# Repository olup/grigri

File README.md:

# grigri
Grigri - the open storyteller

<p xmlns:cc="http://creativecommons.org/ns#" xmlns:dct="http://purl.org/dc/terms/"><a property="dct:title" rel="cc:attributionURL" href="https://github.com/olup/grigri">Grigri</a> by <a rel="cc:attributionURL dct:creator" property="cc:attributionName" href="https://github.com/olup">the grigri team</a> is licensed under <a href="http://creativecommons.org/licenses/by-nc/4.0/?ref=chooser-v1" target="_blank" rel="license noopener noreferrer" style="display:inline-block;">CC BY-NC 4.0</a></p>

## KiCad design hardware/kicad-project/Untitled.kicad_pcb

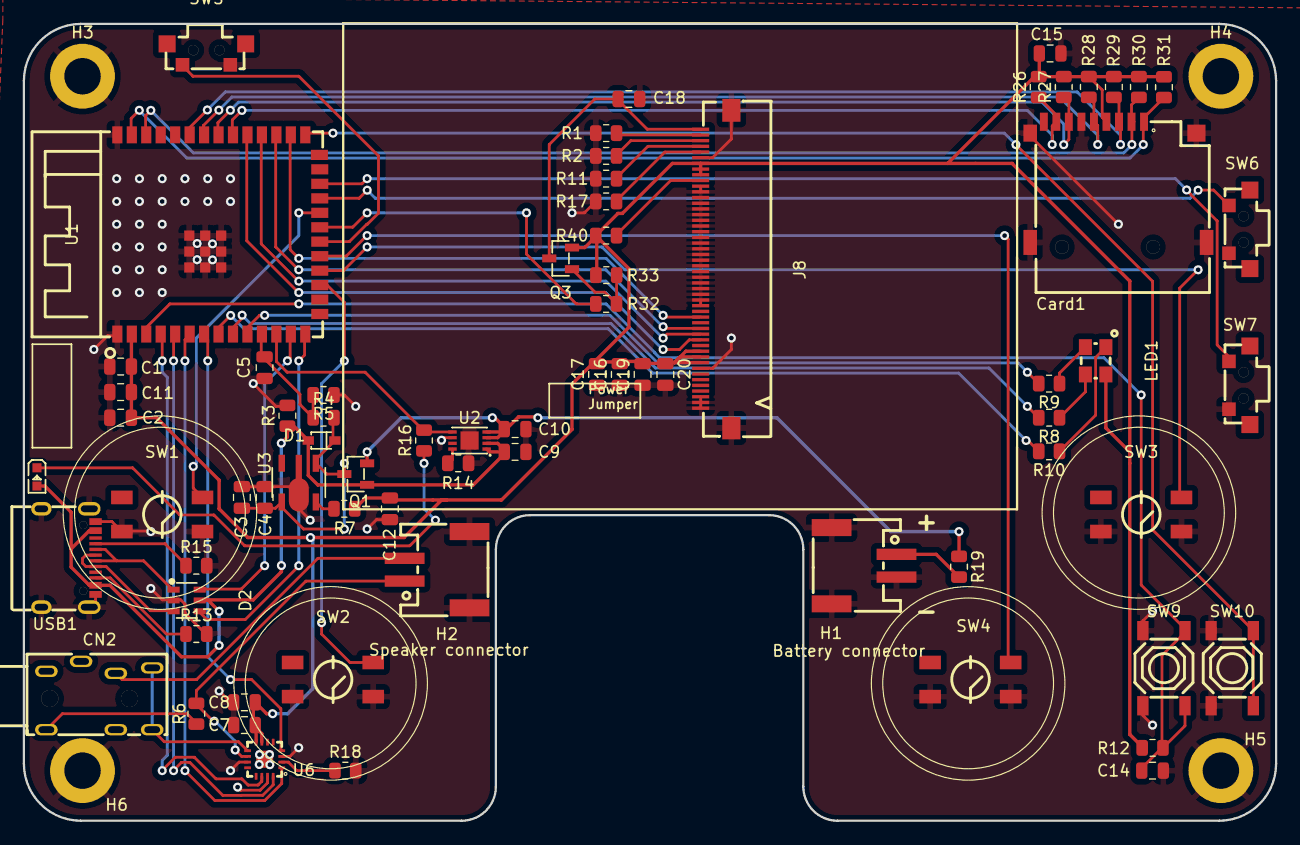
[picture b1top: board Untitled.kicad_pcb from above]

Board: 2 copper layers, 110.0 x 70.0 mm, 75 parts (0 on the bottom side), 59 nets.

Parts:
C1, C2, C3, C7, C15, C16, C17, C18, C19: 10uF; C_0805_2012Metric
C4, C12: 10uf; C_0805_2012Metric
C5, C20: 100nF; C_0805_2012Metric
C8: 0.1uF; C_0805_2012Metric
C9, C10: 4.7uF; C_0805_2012Metric
C11: 1uF; C_0805_2012Metric
C14: 1uf; C_0805_2012Metric
CHARGE_LED1: KT-0603R; LED0603-RD
CN2: ST-0322D00-071-1A2H; AUDIO-TH_ST-0322D00-071-1A2H
Card1: TF PUSH; TF-SMD_TF-PUSH
D1: 1N5819WS; SOD-323_L1.8-W1.3-LS2.5-RD
D2: USBLC6-2SC6_C2687116; SOT-23-6_L2.9-W1.6-P0.95-LS2.8-BL
H1: Battery connector; CONN-SMD_2P-P2.00_XUNPU_WAFER-PH2.0-2PWB
H2: Speaker connector; CONN-SMD_2P-P2.00_XUNPU_WAFER-PH2.0-2PWB
H3, H4, H5, H6: mhole; MountingHole_3.2mm_M3_ISO7380_Pad
J8: Conn_01x50; FPC-SMD_AFC01-S50FCC-00
LED1: E6C1209RGBC3UDA; LED-ARRAY-SMD_4P-L3.2-W2.7-TL-1
Q1, Q3: DMG2301L-7; SOT-23-3_L2.9-W1.3-P1.90-LS2.4-BR
R1, R2, R11, R17: 10; R_0805_2012Metric
R3, R12, R26, R27, R28, R29, R30, R31, R40: 10k; R_0805_2012Metric
R4, R5: 1M; R_0805_2012Metric
R6, R32: 330; R_0805_2012Metric
R7, R18, R19: 0; R_0805_2012Metric
R8, R9: 30; R_0805_2012Metric
R10: 120; R_0805_2012Metric
R13, R15: 5.1k; R_0805_2012Metric
R14: 3k; R_0805_2012Metric
R16: 2K2; R_0805_2012Metric
R33: 100k; R_0805_2012Metric
SW1, SW2, SW3, SW4: K2-1109SP-C4SA; KEY-SMD_4P-L4.5-W4.5-P3.00-LS7.0
SW5, SW6, SW7: GT-TC054C-H035-L1W; KEY-SMD_4P-L7.8-W2.8-P4.20-EH
SW9, SW10: TS-1187A-B-A-B; SW-SMD_4P-L5.1-W5.1-P3.70-LS6.5-TL-2
U1: ESP32-S3-WROOM-1(N8R2); WIRELM-SMD_ESP32-S3-WROOM-1
U2: MCP73831-2ACI/MC; TDFN-8_L3.0-W2.0-P0.50-BL-EP1.6
U3: ME6217C33P5G; SOT-89-5_L4.5-W2.5-P1.50-LS4.5-BR
U6: MAX98357AETE+T; TQFN-16_L3.0-W3.0-P0.50-BL-EP1.5
USB1: TYPE-C 16PIN 2MD(073); USB-C-SMD_TYPE-C-6PIN-2MD-073

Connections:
+3.3V: C1.2, C2.2, C7.2, C8.2, C11.2, C12.2, C15.2, C16.2, C17.2, C19.2, C20.1, Card1.4 (VDD), J8.7, J8.8, J8.9, J8.40, J8.41, J8.42 (Pin_41), LED1.2, Q3.2 (S), R7.1, R12.1, R26.2, R27.2, R28.2, R29.2, R30.2, R31.2, R33.2, R40.1, U1.2 (3V3), U6.7 (VDD), U6.8 (VDD)
+5V: C9.1, CHARGE_LED1.2 (A), D1.2 (A), D2.5 (VBUS), Q1.1 (G), R3.1, U2.1 (VDD), U2.2 (VDD), USB1.2 (VBUS), USB1.11 (VBUS)
+BATT: C10.1, Q1.2 (S), R19.1, U2.3 (VBAT), U2.4 (VBAT)
AMP_EN: U1.7 (IO7), U6.4 (~SD_MODE)
BAT_CHARGING_STAT: R16.2, U1.12 (IO8), U2.5 (STAT)
BAT_READ: C5.2, R4.1, R5.2, U1.11 (IO18)
BOOT: SW10.1 (A), SW10.2 (B), U1.27 (IO0)
BTN_1: SW1.3, U1.22 (IO14)
BTN_2: SW2.3, U1.17 (IO9)
BTN_3: SW3.3, U1.18 (IO10)
BTN_4: SW4.3, U1.19 (IO11)
BTN_5: SW5.1, U1.20 (IO12)
BTN_6: SW6.1, U1.23 (IO21)
BTN_7: SW7.1, U1.24 (IO47)
EN: C14.1, R12.2, SW9.1 (A), SW9.2 (B), U1.3 (EN)
GND: C1.1, C2.1, C3.1, C4.1, C5.1, C7.1, C8.1, C9.2, C10.2, C11.1, C12.1, C14.2, C15.1, C16.1, C17.1, C18.1, C19.1, C20.2, Card1.6 (VSS), Card1.10, Card1.11, Card1.12, Card1.13, D2.2 (GND), H1.2, H1.4, H1.5, H2.4, H2.5, H3.1, H4.1, H5.1, H6.1, J8.6, J8.11, J8.12, J8.13, J8.14, J8.15, J8.16, J8.17, J8.18, J8.19, J8.20, J8.21, J8.22, J8.23, J8.24, J8.25, J8.26, J8.27, J8.28, J8.29, J8.30, J8.31, J8.32, J8.43, J8.48, J8.49, J8.50, J8.51 (MP), J8.52 (MP), R1.2, R2.2, R3.2, R5.1, R11.2, R13.2, R14.2, R15.2, R17.2, R18.2, SW1.1, SW1.2, SW2.1, SW2.2, SW3.1, SW3.2, SW4.1, SW4.2, SW5.2, SW6.2, SW7.2, SW9.3 (C), SW9.4 (D), SW10.3 (C), SW10.4 (D), U1.1 (GND), U1.40 (GND), U1.41 (GND), U2.6 (VSS), U2.9 (EP), U3.2 (VSS), U6.3 (GND), U6.11 (GND), U6.15 (GND), U6.17 (EP), USB1.1 (GND), USB1.12 (GND), USB1.13 (SHELL), USB1.14 (SHELL)
GPIO_19: D2.6 (I/O1), U1.13 (IO19)
GPIO_20: D2.4 (I/O2), U1.14 (IO20)
I2S_BCLK: U1.5 (IO5), U6.16 (BCLK)
I2S_DOUT: U1.6 (IO6), U6.1 (DIN)
I2S_LRCLK: U1.4 (IO4), U6.14 (LRCLK)
LCD_BL: R32.2, U1.21 (IO13)
LCD_CS: J8.38, U1.31 (IO38)
LCD_DC: J8.36, U1.29 (IO36)
LCD_MOSI: J8.34, U1.28 (IO35)
LCD_SCK: J8.37, U1.30 (IO37)
LED_RGB_BLUE: R8.2, U1.9 (IO16)
LED_RGB_GREEN: R9.2, U1.10 (IO17)
LED_RGB_RED: R10.2, U1.8 (IO15)
unnamed: CHARGE_LED1.1 (K), R16.1
unnamed: CN2.1, R6.1
unnamed: CN2.5, H2.2
unnamed: C3.2, C4.2, D1.1 (K), Q1.3 (D), R4.2, U3.1 (CE), U3.4 (VIN)
unnamed: H1.1, R19.2
unnamed: C18.2, J8.1, Q3.3 (D)
unnamed: J8.2, R1.1
unnamed: J8.3, R2.1
unnamed: J8.4, R11.1
unnamed: J8.5, R17.1
unnamed: J8.10, R40.2
unnamed: LED1.1, R10.1
unnamed: LED1.3, R9.1
unnamed: LED1.4, R8.1
unnamed: Q3.1 (G), R32.1, R33.1
unnamed: R14.1, U2.8 (PROG)
unnamed: R7.2, U3.5 (VOUT)
unnamed: R18.1, U6.2 (GAIN_SLOT)
unnamed: H2.1, R6.2, U6.10 (OUTN)
unnamed: CN2.3, CN2.4, U6.9 (OUTP)
unnamed: R15.1, USB1.4 (CC1)
unnamed: R13.1, USB1.10 (CC2)
unnamed: D2.1 (I/O1), USB1.5 (DN2), USB1.7 (DN1)
unnamed: D2.3 (I/O2), USB1.6 (DP1), USB1.8 (DP2)
SD_CLK: Card1.5 (CLX), R28.1, U1.34 (IO41)
SD_CMD: Card1.3 (CMD), R29.1, U1.35 (IO42)
SD_DAT_0: Card1.7 (DAT0), R27.1, U1.33 (IO40)
SD_DAT_1: Card1.8 (DAT1), R26.1, U1.32 (IO39)
SD_DAT_2: Card1.1 (DAT2), R31.1, U1.39 (IO1)
SD_DAT_3: Card1.2 (CD/DAT3), R30.1, U1.38 (IO2)

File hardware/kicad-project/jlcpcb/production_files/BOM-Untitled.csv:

Comment,Designator,Footprint,LCSC
DMG2301L-7,"Q1,Q3",SOT-23-3_L2.9-W1.3-P1.90-LS2.4-BR,C102619
MCP73831-2ACI/MC,U2,TDFN-8_L3.0-W2.0-P0.50-BL-EP1.6,C150772
1N5819WS,D1,SOD-323_L1.8-W1.3-LS2.5-RD,C191023
KT-0603R,CHARGE_LED1,LED0603-RD,C2286
USBLC6-2SC6_C2687116,D2,SOT-23-6_L2.9-W1.6-P0.95-LS2.8-BL,C2687116
TYPE-C 16PIN 2MD(073),USB1,USB-C-SMD_TYPE-C-6PIN-2MD-073,C2765186
ST-0322D00-071-1A2H,CN2,AUDIO-TH_ST-0322D00-071-1A2H,C2829970
ESP32-S3-WROOM-1(N8R2),U1,WIRELM-SMD_ESP32-S3-WROOM-1,C2913204
GT-TC054C-H035-L1W,"SW5,SW6,SW7",KEY-SMD_4P-L7.8-W2.8-P4.20-EH,C3020033
Battery connector,"H1,H2",CONN-SMD_2P-P2.00_XUNPU_WAFER-PH2.0-2PWB,C3029440
TS-1187A-B-A-B,"SW10,SW9",SW-SMD_4P-L5.1-W5.1-P3.70-LS6.5-TL-2,C318884
E6C1209RGBC3UDA,LED1,LED-ARRAY-SMD_4P-L3.2-W2.7-TL-1,C375572
TF PUSH,Card1,TF-SMD_TF-PUSH,C393941
ME6217C33P5G,U3,SOT-89-5_L4.5-W2.5-P1.50-LS4.5-BR,C81592
MAX98357AETE+T,U6,TQFN-16_L3.0-W3.0-P0.50-BL-EP1.5,C910544
K2-1109SP-C4SA,"SW1,SW2,SW3,SW4",KEY-SMD_4P-L4.5-W4.5-P3.00-LS7.0,C92570
3k,R14,R_0805_2012Metric,
10k,R27,R_0805_2012Metric,
10k,R3,R_0805_2012Metric,
10k,R31,R_0805_2012Metric,
10uF,C18,C_0805_2012Metric,
mhole,H5,MountingHole_3.2mm_M3_ISO7380_Pad,
10uF,C19,C_0805_2012Metric,
10,R1,R_0805_2012Metric,
0.1uF,C8,C_0805_2012Metric,
mhole,H6,MountingHole_3.2mm_M3_ISO7380_Pad,
1M,R5,R_0805_2012Metric,
1uF,C11,C_0805_2012Metric,
10uF,C3,C_0805_2012Metric,
10uF,C2,C_0805_2012Metric,
10k,R28,R_0805_2012Metric,
10k,R40,R_0805_2012Metric,
10,R17,R_0805_2012Metric,
5.1k,R15,R_0805_2012Metric,
1M,R4,R_0805_2012Metric,
100nF,C20,C_0805_2012Metric,
10uF,C17,C_0805_2012Metric,
4.7uF,C10,C_0805_2012Metric,
4.7uF,C9,C_0805_2012Metric,
10uf,C12,C_0805_2012Metric,
10k,R29,R_0805_2012Metric,
mhole,H3,MountingHole_3.2mm_M3_ISO7380_Pad,
10k,R12,R_0805_2012Metric,
10uF,C7,C_0805_2012Metric,
Conn_01x50,J8,FPC-SMD_AFC01-S50FCC-00,
10,R2,R_0805_2012Metric,
2K2,R16,R_0805_2012Metric,
10k,R30,R_0805_2012Metric,
mhole,H4,MountingHole_3.2mm_M3_ISO7380_Pad,
0,R18,R_0805_2012Metric,
30,R8,R_0805_2012Metric,
100k,R33,R_0805_2012Metric,
330,R6,R_0805_2012Metric,
10k,R26,R_0805_2012Metric,
5.1k,R13,R_0805_2012Metric,
10uF,C16,C_0805_2012Metric,
1uf,C14,C_0805_2012Metric,
0,R19,R_0805_2012Metric,
10,R11,R_0805_2012Metric,
10uF,C1,C_0805_2012Metric,
30,R9,R_0805_2012Metric,
330,R32,R_0805_2012Metric,
120,R10,R_0805_2012Metric,
100nF,C5,C_0805_2012Metric,
10uf,C4,C_0805_2012Metric,
10uF,C15,C_0805_2012Metric,
0,R7,R_0805_2012Metric,

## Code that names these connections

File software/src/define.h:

#pragma once

// buttons
#define BTN_1 14
#define BTN_2 9
#define BTN_3 10
#define BTN_4 11
#define BTN_5 12
#define BTN_6 21
#define BTN_7 47

#define WAKE_UP_BTN GPIO_NUM_12

// sound
#define I2S_DOUT 6
#define I2S_BCLK 5
#define I2S_LRC 4

#define AMP_EN 7

// display
// display definition is overriden by the Pio build env, set it there. cf:
// https://github.com/Bodmer/TFT_eSPI/blob/master/docs/PlatformIO/Configuring%20options.txt
#define LCD_BL 13

// sd card
#define CLK 41
#define CMD 42
#define D0 40
#define D1 39
#define D2 1
#define D3 2

// battery
#define BATTERY_READ 18
#define BATTERY_CHARGING_STAT 8

// led
#define LED_RGB_RED 15
#define LED_RGB_GREEN 17
#define LED_RGB_BLUE 16

#define AUDIO_LOG 1

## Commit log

2023-10-21 Remove 'backups' directory from tracking
2023-10-21 add outputs
2023-10-21 rev1
2023-10-21 remove pck files
2023-10-21 REmove lck files
2023-10-21 remove lck
2023-10-21 reset schemtics to rev1
2023-10-21 outputs
2023-10-21 add project archive
2023-10-21 add archive
2023-10-25 update MAX sdmode to 634k R
2023-10-26 fix mosfet
2023-11-07 routing
2023-11-08 New side buttons
2023-11-08 update pdf
2023-11-27 exports
2023-12-06 rev2 almost there
2023-12-09 REV2
2023-12-09 rev 4
2023-12-28 Integrate software
2023-12-28 Auto switch off
2023-12-28 prevent going back when cover node
2023-12-31 feat: print wakeup reason
2024-01-01 disable brownout
2024-01-01 ignore .vscode
2024-01-01 Update todo
2024-01-01 better switch off
2024-01-01 fix sleep
2024-01-02 draw jpeg
2024-01-04 deep sleep amp off
2024-01-04 display pause
2024-01-04 pause
2024-01-05 small fixes
2024-01-05 remove vscode from tracking
2024-01-06 PWM frequency change
2024-01-06 fix siund off
2024-01-06 persist wifi password
2024-01-07 persist player position and cacel switch off on config mode
2024-01-07 rehydrate plaback position
2024-01-08 more state
2024-01-08 take settings into account
2024-01-08 persist settings
2024-01-08 perisst nav
2024-01-09 not usefull
2024-01-10 targz
2024-01-12 test-build
2024-01-14 web server updates
2024-02-24 change of LDO in schematics
